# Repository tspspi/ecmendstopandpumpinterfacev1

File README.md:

# ECM 12V endstop and pump interface

This is a simple interface board between the 5V ECM logic and the 10 12V endstop
sensors as well as the 4 12V DC pump interfaces.

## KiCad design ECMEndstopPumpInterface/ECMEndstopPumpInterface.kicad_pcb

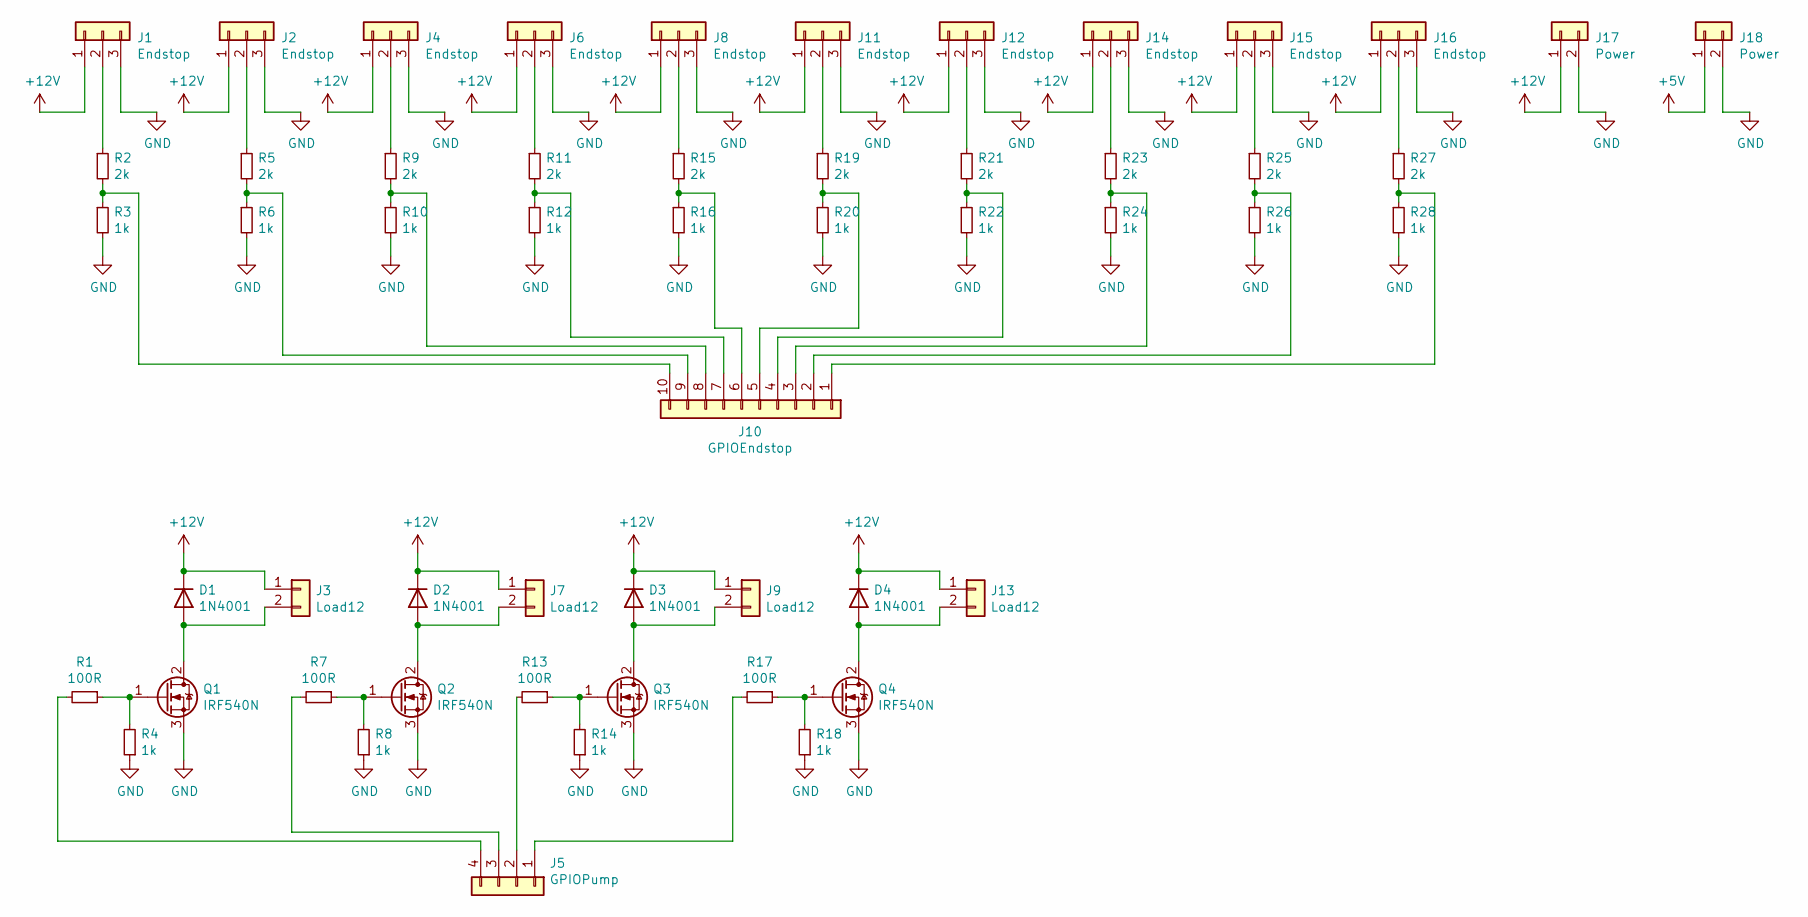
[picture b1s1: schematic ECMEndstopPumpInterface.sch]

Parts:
D1, D2, D3, D4: 1N4001; D_DO-41_SOD81_P10.16mm_Horizontal
J1, J2, J4, J6, J8, J11, J12, J14, J15, J16: Endstop; PinHeader_1x03_P2.54mm_Vertical
J3, J7, J9, J13: Load12; PinHeader_1x02_P2.54mm_Vertical
J5: GPIOPump; PinHeader_1x04_P2.54mm_Vertical
J10: GPIOEndstop; PinHeader_1x10_P2.54mm_Vertical
J17, J18: Power; PinHeader_1x02_P2.54mm_Vertical
Q1, Q2, Q3, Q4: IRF540N; TO-220-3_Vertical
R1, R7, R13, R17: 100R; R_Axial_DIN0411_L9.9mm_D3.6mm_P12.70mm_Horizontal
R2, R5, R9, R11, R15, R19, R21, R23, R25, R27: 2k; R_Axial_DIN0411_L9.9mm_D3.6mm_P12.70mm_Horizontal
R3, R4, R6, R8, R10, R12, R14, R16, R18, R20, R22, R24, R26, R28: 1k; R_Axial_DIN0411_L9.9mm_D3.6mm_P12.70mm_Horizontal

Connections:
+5V: J18.1
+12V: D1.1 (K), D2.1 (K), D3.1 (K), D4.1 (K), J1.1, J2.1, J3.1, J4.1, J6.1, J7.1, J8.1, J9.1, J11.1, J12.1, J13.1, J14.1, J15.1, J16.1, J17.1
GND: J1.3, J2.3, J4.3, J6.3, J8.3, J11.3, J12.3, J14.3, J15.3, J16.3, J17.2, J18.2, Q1.3 (S), Q2.3 (S), Q3.3 (S), Q4.3 (S), R3.2, R4.1, R6.2, R8.1, R10.2, R12.2, R14.1, R16.2, R18.1, R20.2, R22.2, R24.2, R26.2, R28.2
unnamed: D1.2 (A), J3.2, Q1.2 (D)
unnamed: D2.2 (A), J7.2, Q2.2 (D)
unnamed: D3.2 (A), J9.2, Q3.2 (D)
unnamed: D4.2 (A), J13.2, Q4.2 (D)
unnamed: J1.2, R2.1
unnamed: J2.2, R5.1
unnamed: J4.2, R9.1
unnamed: J5.1, R17.2
unnamed: J5.2, R13.2
unnamed: J5.3, R7.2
unnamed: J5.4, R1.2
unnamed: J6.2, R11.1
unnamed: J8.2, R15.1
unnamed: J10.1, R27.2, R28.1
unnamed: J10.2, R25.2, R26.1
unnamed: J10.3, R23.2, R24.1
unnamed: J10.4, R21.2, R22.1
unnamed: J10.5, R19.2, R20.1
unnamed: J10.6, R15.2, R16.1
unnamed: J10.7, R11.2, R12.1
unnamed: J10.8, R9.2, R10.1
unnamed: J10.9, R5.2, R6.1
unnamed: J10.10, R2.2, R3.1
unnamed: J11.2, R19.1
unnamed: J12.2, R21.1
unnamed: J14.2, R23.1
unnamed: J15.2, R25.1
unnamed: J16.2, R27.1
unnamed: Q1.1 (G), R1.1, R4.2
unnamed: Q2.1 (G), R7.1, R8.2
unnamed: Q3.1 (G), R13.1, R14.2
unnamed: Q4.1 (G), R17.1, R18.2

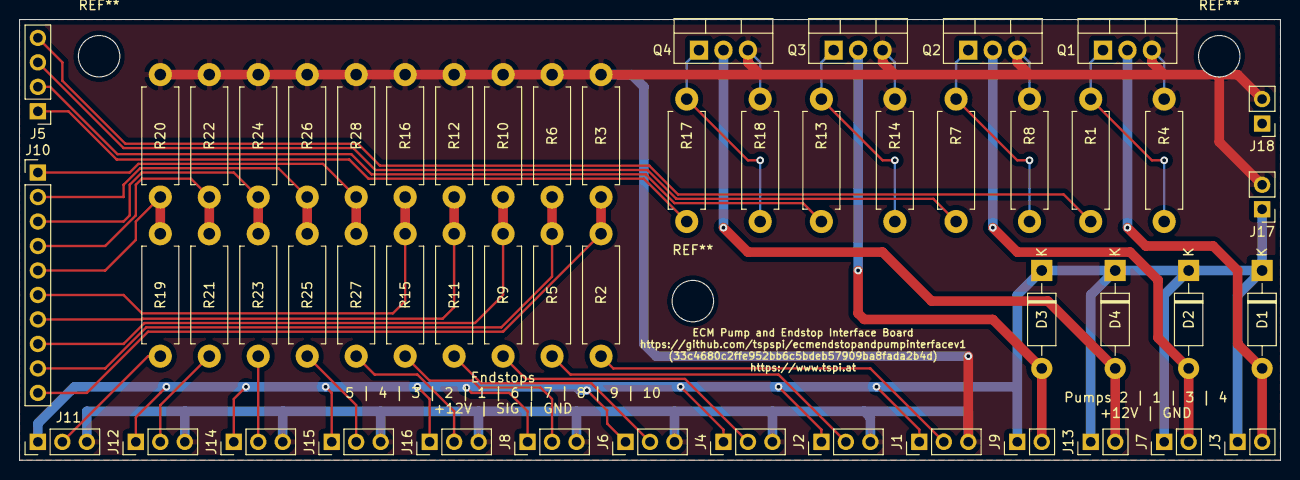
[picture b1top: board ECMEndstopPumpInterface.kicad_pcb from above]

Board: 2 copper layers, 130.8 x 45.7 mm, 54 parts (0 on the bottom side), 34 nets.

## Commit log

2023-04-02 Adding README and LICENSE
2023-04-02 Adding Gerber files
2023-04-02 Adding top side rendering
2023-04-02 Adding rendering to README
